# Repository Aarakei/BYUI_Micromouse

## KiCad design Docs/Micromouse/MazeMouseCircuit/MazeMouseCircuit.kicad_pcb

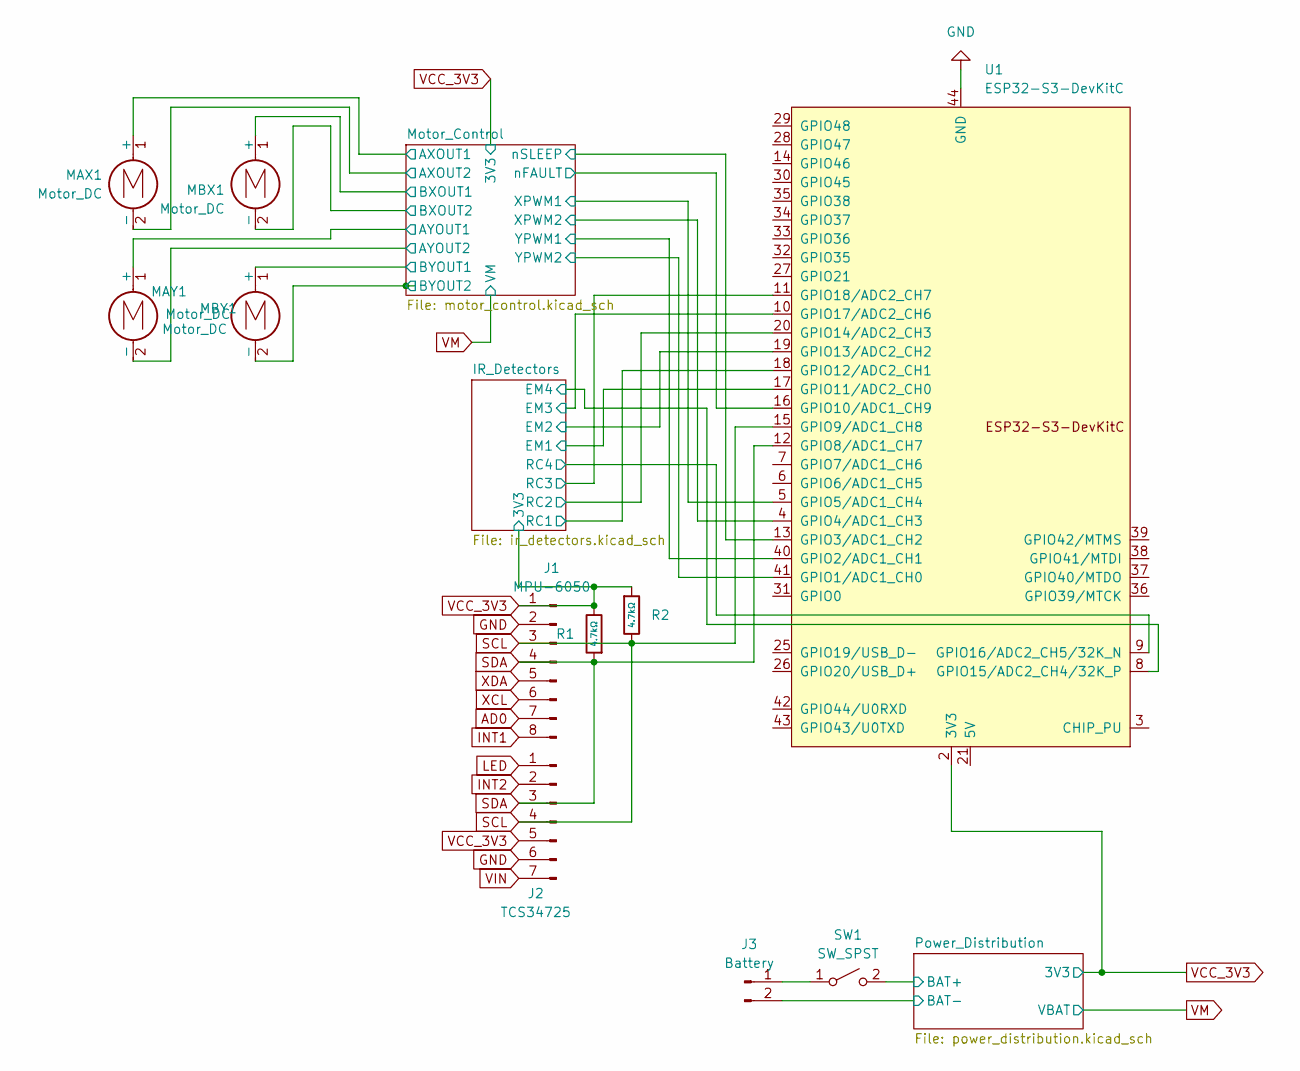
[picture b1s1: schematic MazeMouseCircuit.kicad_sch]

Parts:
J1: MPU-6050; PinHeader_1x08_P2.54mm_Vertical
J2: TCS34725; PinHeader_1x07_P2.54mm_Vertical
J3: Battery; PhoenixContact_GMSTBVA_2,5_2-G_1x02_P7.50mm_Vertical
MAX1: Motor_DC; PinHeader_2x01_P2.54mm_Vertical
MAY1: Motor_DC; PinHeader_2x01_P2.54mm_Vertical
MBX1: Motor_DC; PinHeader_2x01_P2.54mm_Vertical
MBY1: Motor_DC; PinHeader_2x01_P2.54mm_Vertical
R1, R2: 4.7kΩ; R_0402; Overload Voltage (Max) 50V; Tolerance ±1%; Part 0402WGF4701TCE; LCSC C25900
SW1: SW_SPST; SW_DIP_SPSTx01_Slide_9.78x4.72mm_W8.61mm_P2.54mm
U1: ESP32-S3-DevKitC; ESP32-S3-DevKitC-Dual-USB-C

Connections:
/IR_Detectors/EM1: U1.17 (GPIO11/ADC2_CH0); also elsewhere on the board
/IR_Detectors/EM2: U1.19 (GPIO13/ADC2_CH2); also elsewhere on the board
/IR_Detectors/EM3: U1.10 (GPIO17/ADC2_CH6); also elsewhere on the board
/IR_Detectors/EM4: U1.8 (GPIO15/ADC2_CH4/32K_P); also elsewhere on the board
/IR_Detectors/RC1: U1.18 (GPIO12/ADC2_CH1); also elsewhere on the board
/IR_Detectors/RC2: U1.20 (GPIO14/ADC2_CH3); also elsewhere on the board
/IR_Detectors/RC3: U1.11 (GPIO18/ADC2_CH7); also elsewhere on the board
/IR_Detectors/RC4: U1.9 (GPIO16/ADC2_CH5/32K_N); also elsewhere on the board
/Motor_Control/AXOUT1: MAX1.1 (+); also elsewhere on the board
/Motor_Control/AXOUT2: MAX1.2 (-); also elsewhere on the board
/Motor_Control/AYOUT1: MAY1.1 (+); also elsewhere on the board
/Motor_Control/AYOUT2: MAY1.2 (-); also elsewhere on the board
/Motor_Control/BXOUT1: MBX1.1 (+); also elsewhere on the board
/Motor_Control/BXOUT2: MBX1.2 (-); also elsewhere on the board
/Motor_Control/BYOUT1: MBY1.1 (+); also elsewhere on the board
/Motor_Control/BYOUT2: MBY1.2 (-); also elsewhere on the board
/Motor_Control/XPWM1: U1.5 (GPIO5/ADC1_CH4); also elsewhere on the board
/Motor_Control/XPWM2: U1.4 (GPIO4/ADC1_CH3); also elsewhere on the board
/Motor_Control/YPWM1: U1.40 (GPIO2/ADC1_CH1); also elsewhere on the board
/Motor_Control/YPWM2: U1.41 (GPIO1/ADC1_CH0); also elsewhere on the board
/Motor_Control/nFAULT: U1.16 (GPIO10/ADC1_CH9); also elsewhere on the board
/Motor_Control/nSLEEP: U1.13 (GPIO3/ADC1_CH2); also elsewhere on the board
/Power_Distribution/BAT+: SW1.2 (B); also elsewhere on the board
AD0: J1.7
GND: J1.2, J2.6, J3.2, U1.22 (GND), U1.23 (GND), U1.24 (GND), U1.44 (GND); also elsewhere on the board
INT1: J1.8
INT2: J2.2
LED: J2.1
unnamed: J3.1, SW1.1 (A)
SCL: J1.3, J2.4, R2.2, U1.15 (GPIO9/ADC1_CH8)
SDA: J1.4, J2.3, R1.1, U1.12 (GPIO8/ADC1_CH7)
VCC_3V3: J1.1, J2.5, R1.2, R2.1, U1.1 (3V3), U1.2 (3V3); also elsewhere on the board
VIN: J2.7
XCL: J1.6
XDA: J1.5

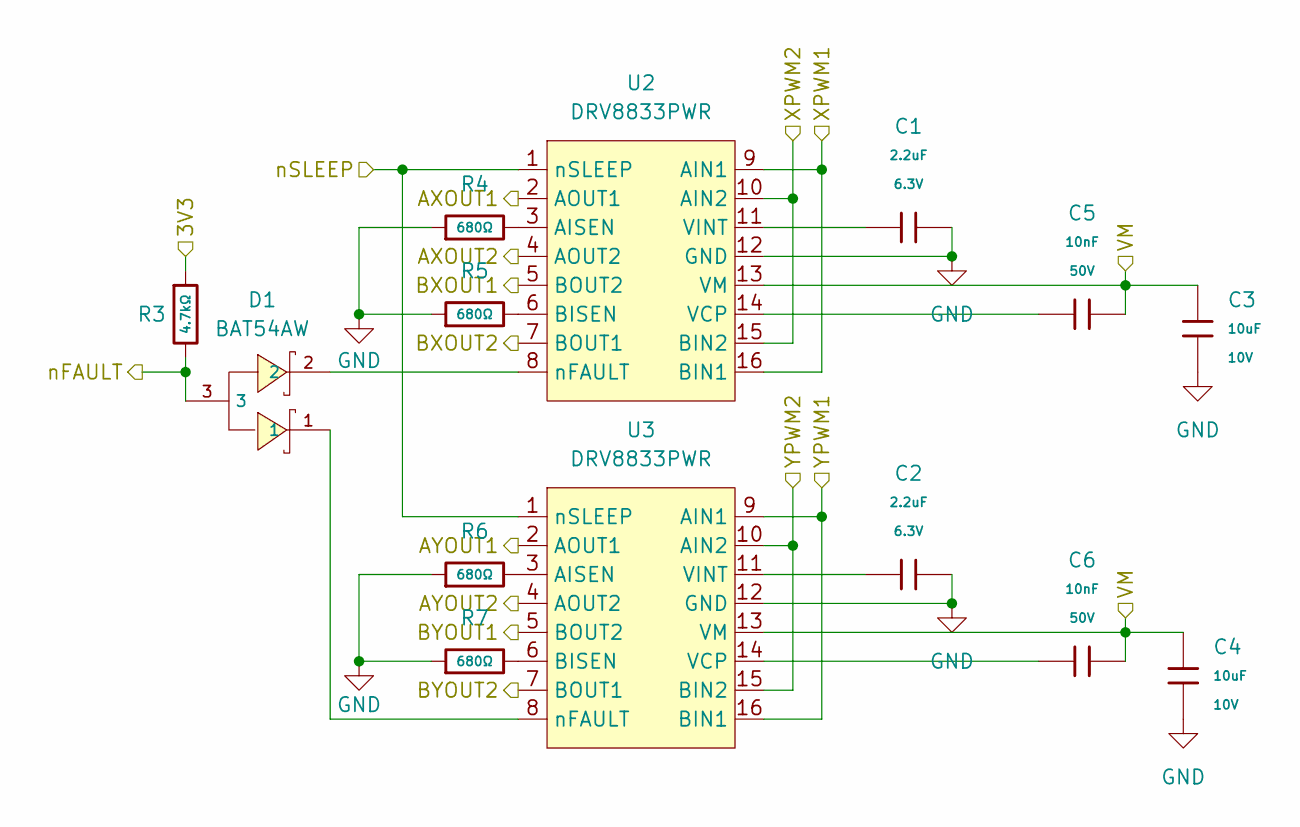
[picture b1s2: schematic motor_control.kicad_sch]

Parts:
C1, C2: 2.2uF; C_0402; Voltage Rated 6.3V; Tolerance ±20%; Part CL05A225MQ5NSNC; LCSC C12530
C3, C4: 10uF; C_0603; Voltage Rated 10V; Tolerance ±10%; Part CL10A106KP8NNNC; LCSC C19702
C5, C6: 10nF; C_0402; Voltage Rated 50V; Tolerance ±10%; Part CL05B103KB5NNNC; LCSC C15195
D1: BAT54AW; SOT-323-3_L2.0-W1.3-P1.30-LS2.3-BR; Part BAT54AW; LCSC C22466374
R3: 4.7kΩ; R_0402; Overload Voltage (Max) 50V; Tolerance ±1%; Part 0402WGF4701TCE; LCSC C25900
R4, R5, R6, R7: 680Ω; R_0402; Overload Voltage (Max) 50V; Tolerance ±1%; Part 0402WGF6800TCE; LCSC C25130
U2, U3: DRV8833PWR; TSSOP-16_4.4x5mm_P0.65mm

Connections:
/Motor_Control/AXOUT1: U2.2 (AOUT1); also elsewhere on the board
/Motor_Control/AXOUT2: U2.4 (AOUT2); also elsewhere on the board
/Motor_Control/AYOUT1: U3.2 (AOUT1); also elsewhere on the board
/Motor_Control/AYOUT2: U3.4 (AOUT2); also elsewhere on the board
/Motor_Control/BXOUT1: U2.5 (BOUT2); also elsewhere on the board
/Motor_Control/BXOUT2: U2.7 (BOUT1); also elsewhere on the board
/Motor_Control/BYOUT1: U3.5 (BOUT2); also elsewhere on the board
/Motor_Control/BYOUT2: U3.7 (BOUT1); also elsewhere on the board
/Motor_Control/XPWM1: U2.9 (AIN1), U2.16 (BIN1); also elsewhere on the board
/Motor_Control/XPWM2: U2.10 (AIN2), U2.15 (BIN2); also elsewhere on the board
/Motor_Control/YPWM1: U3.9 (AIN1), U3.16 (BIN1); also elsewhere on the board
/Motor_Control/YPWM2: U3.10 (AIN2), U3.15 (BIN2); also elsewhere on the board
/Motor_Control/nFAULT: D1.3, R3.2; also elsewhere on the board
/Motor_Control/nSLEEP: U2.1 (nSLEEP), U3.1 (nSLEEP); also elsewhere on the board
GND: C1.2, C2.2, C3.1, C4.1, R4.1, R5.1, R6.1, R7.1, U2.12 (GND), U3.12 (GND); also elsewhere on the board
unnamed: R4.2, U2.3 (AISEN)
unnamed: R5.2, U2.6 (BISEN)
unnamed: C5.2, U2.14 (VCP)
unnamed: C1.1, U2.11 (VINT)
unnamed: D1.2, U2.8 (nFAULT)
unnamed: R6.2, U3.3 (AISEN)
unnamed: R7.2, U3.6 (BISEN)
unnamed: C6.2, U3.14 (VCP)
unnamed: C2.1, U3.11 (VINT)
unnamed: D1.1, U3.8 (nFAULT)
VCC_3V3: R3.1; also elsewhere on the board
VM: C3.2, C4.2, C5.1, C6.1, U2.13 (VM), U3.13 (VM); also elsewhere on the board

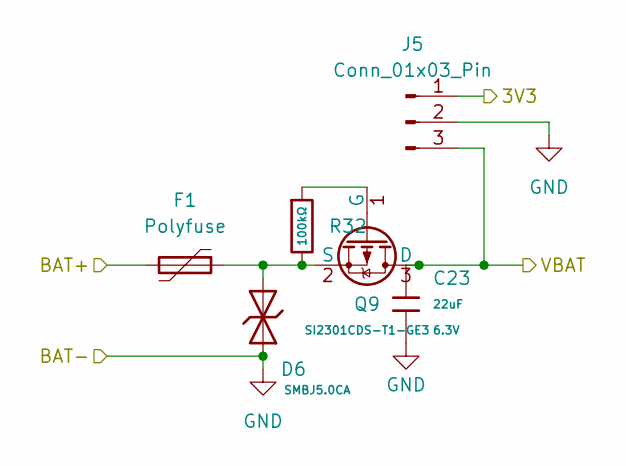
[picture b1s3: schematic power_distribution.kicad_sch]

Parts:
C23: 22uF; C_0603; Voltage Rated 6.3V; Tolerance ±20%; Part CL10A226MQ8NRNC; LCSC C59461
D6: SMBJ5.0CA; D_SMB; Part SMBJ5.0CA; LCSC C19077559
F1: Polyfuse; Fuse_0402_1005Metric
J5: Conn_01x03_Pin; PinHeader_1x03_P2.54mm_Vertical
Q9: SI2301CDS-T1-GE3; Q_SOT-23; Part SI2301CDS-T1-GE3; LCSC C10487
R32: 100kΩ; R_0603; Overload Voltage (Max) 75V; Tolerance ±1%; Part 0603WAF1003T5E; LCSC C25803

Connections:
/Power_Distribution/BAT+: F1.2; also elsewhere on the board
GND: C23.2, D6.2, J5.2; also elsewhere on the board
unnamed: Q9.1 (G), R32.1
unnamed: D6.1, F1.1, Q9.2 (S), R32.2
VCC_3V3: J5.1; also elsewhere on the board
VM: C23.1, J5.3, Q9.3 (D); also elsewhere on the board

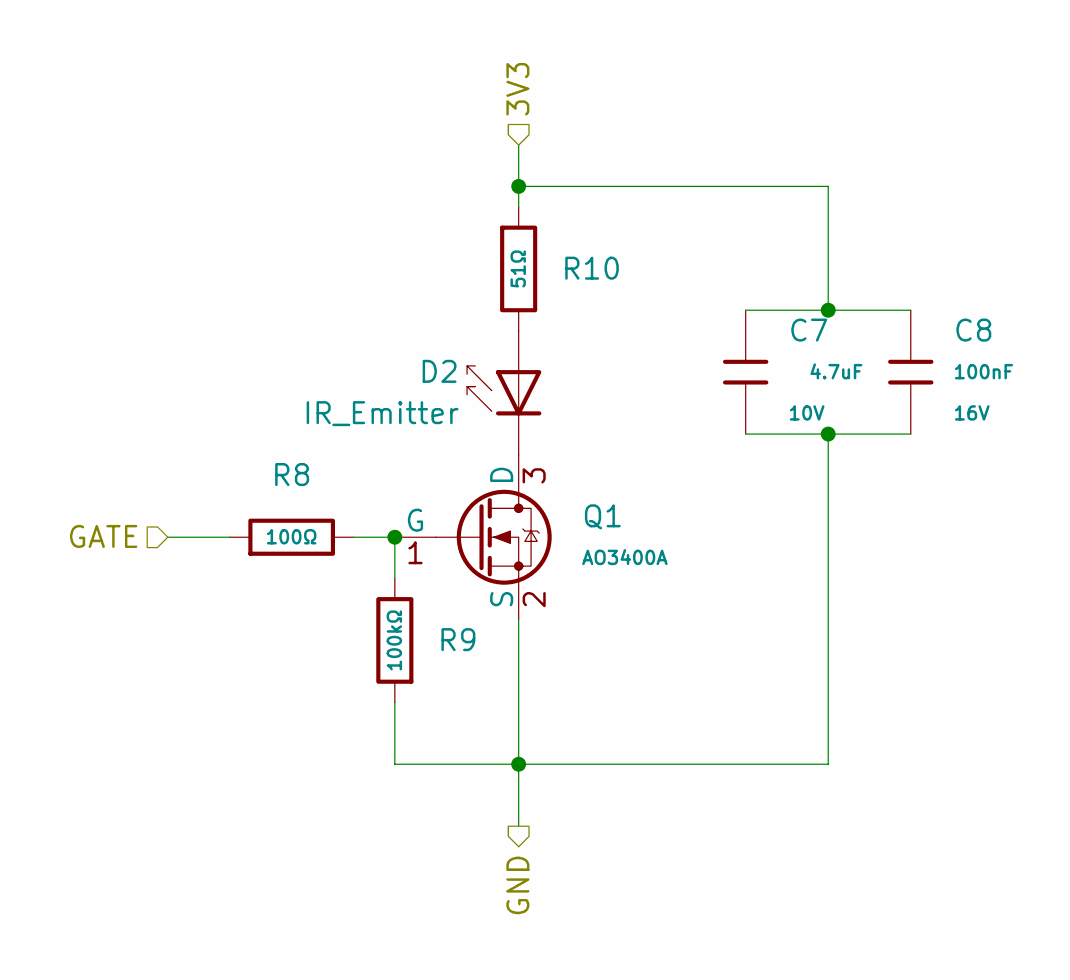
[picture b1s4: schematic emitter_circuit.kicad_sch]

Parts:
C7: 4.7uF; C_0402; Voltage Rated 10V; Tolerance ±20%; Part CL05A475MP5NRNC; LCSC C23733
C8: 100nF; C_0402; Voltage Rated 16V; Tolerance ±10%; Part CL05B104KO5NNNC; LCSC C1525
D2: IR_Emitter; LED_D5.0mm_Horizontal_O1.27mm_Z3.0mm_IRBlack
Q1: AO3400A; Q_SOT-23; Part AO3400A; LCSC C20917
R8: 100Ω; R_0402; Overload Voltage (Max) 50V; Tolerance ±1%; Part 0402WGF1000TCE; LCSC C25076
R9: 100kΩ; R_0603; Overload Voltage (Max) 75V; Tolerance ±1%; Part 0603WAF1003T5E; LCSC C25803
R10: 51Ω; R_0402; Overload Voltage (Max) 50V; Tolerance ±1%; Part 0402WGF510JTCE; LCSC C25125

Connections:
/IR_Detectors/EM1: R8.1; also elsewhere on the board
GND: C7.2, C8.2, Q1.2 (S), R9.1; also elsewhere on the board
unnamed: D2.2 (A), R10.2
unnamed: D2.1 (K), Q1.3 (D)
unnamed: Q1.1 (G), R8.2, R9.2
VCC_3V3: C7.1, C8.1, R10.1; also elsewhere on the board

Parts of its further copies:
C11, C15, C19: 4.7uF; C_0402; Voltage Rated 10V; Tolerance ±20%; Part CL05A475MP5NRNC; LCSC C23733
C12, C16, C20: 100nF; C_0402; Voltage Rated 16V; Tolerance ±10%; Part CL05B104KO5NNNC; LCSC C1525
D3, D4, D5: IR_Emitter; LED_D5.0mm_Horizontal_O1.27mm_Z3.0mm_IRBlack
Q3, Q5, Q7: AO3400A; Q_SOT-23; Part AO3400A; LCSC C20917
R14, R20, R26: 100Ω; R_0402; Overload Voltage (Max) 50V; Tolerance ±1%; Part 0402WGF1000TCE; LCSC C25076
R15, R21, R27: 100kΩ; R_0603; Overload Voltage (Max) 75V; Tolerance ±1%; Part 0603WAF1003T5E; LCSC C25803
R16, R22, R28: 51Ω; R_0402; Overload Voltage (Max) 50V; Tolerance ±1%; Part 0402WGF510JTCE; LCSC C25125

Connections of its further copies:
/IR_Detectors/EM2: R14.1; also elsewhere on the board
/IR_Detectors/EM3: R20.1; also elsewhere on the board
/IR_Detectors/EM4: R26.1; also elsewhere on the board
GND: C11.2, C12.2, C15.2, C16.2, C19.2, C20.2, Q3.2 (S), Q5.2 (S), Q7.2 (S), R15.1, R21.1, R27.1; also elsewhere on the board
unnamed: D3.2 (A), R16.2
unnamed: D3.1 (K), Q3.3 (D)
unnamed: D4.2 (A), R22.2
unnamed: D4.1 (K), Q5.3 (D)
unnamed: D5.2 (A), R28.2
unnamed: D5.1 (K), Q7.3 (D)
unnamed: Q3.1 (G), R14.2, R15.2
unnamed: Q5.1 (G), R20.2, R21.2
unnamed: Q7.1 (G), R26.2, R27.2
VCC_3V3: C11.1, C12.1, C15.1, C16.1, C19.1, C20.1, R16.1, R22.1, R28.1; also elsewhere on the board

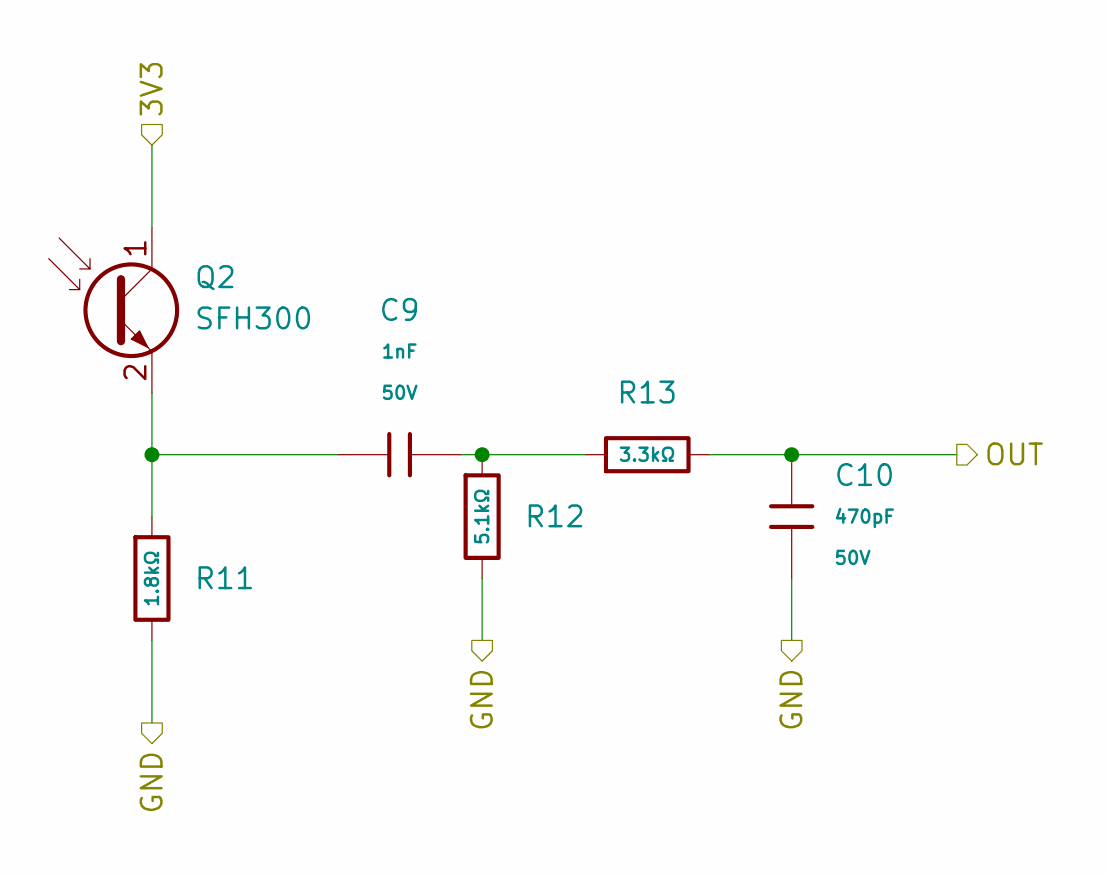
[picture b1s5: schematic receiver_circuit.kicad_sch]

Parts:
C9: 1nF; C_0402; Voltage Rated 50V; Tolerance ±10%; Part 0402B102K500NT; LCSC C1523
C10: 470pF; C_0402; Voltage Rated 50V; Tolerance ±10%; Part 0402B471K500NT; LCSC C1537
Q2: SFH300; LED_D5.0mm_Horizontal_O1.27mm_Z3.0mm_Clear
R11: 1.8kΩ; R_0805; Overload Voltage (Max) 150V; Tolerance ±1%; Part 0805W8F1801T5E; LCSC C17398
R12: 5.1kΩ; R_0402; Overload Voltage (Max) 50V; Tolerance ±1%; Part 0402WGF5101TCE; LCSC C25905
R13: 3.3kΩ; R_0402; Overload Voltage (Max) 50V; Tolerance ±1%; Part 0402WGF3301TCE; LCSC C25890

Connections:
/IR_Detectors/RC1: C10.1, R13.2; also elsewhere on the board
GND: C10.2, R11.2, R12.2; also elsewhere on the board
unnamed: C9.2, R12.1, R13.1
unnamed: C9.1, Q2.2 (E), R11.1
VCC_3V3: Q2.1 (C); also elsewhere on the board

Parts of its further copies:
C13, C17, C21: 1nF; C_0402; Voltage Rated 50V; Tolerance ±10%; Part 0402B102K500NT; LCSC C1523
C14, C18, C22: 470pF; C_0402; Voltage Rated 50V; Tolerance ±10%; Part 0402B471K500NT; LCSC C1537
Q4, Q6, Q8: SFH300; LED_D5.0mm_Horizontal_O1.27mm_Z3.0mm_Clear
R17, R23, R29: 1.8kΩ; R_0805; Overload Voltage (Max) 150V; Tolerance ±1%; Part 0805W8F1801T5E; LCSC C17398
R18, R24, R30: 5.1kΩ; R_0402; Overload Voltage (Max) 50V; Tolerance ±1%; Part 0402WGF5101TCE; LCSC C25905
R19, R25, R31: 3.3kΩ; R_0402; Overload Voltage (Max) 50V; Tolerance ±1%; Part 0402WGF3301TCE; LCSC C25890

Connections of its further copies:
/IR_Detectors/RC2: C14.1, R19.2; also elsewhere on the board
/IR_Detectors/RC3: C18.1, R25.2; also elsewhere on the board
/IR_Detectors/RC4: C22.1, R31.2; also elsewhere on the board
GND: C14.2, C18.2, C22.2, R17.2, R18.2, R23.2, R24.2, R29.2, R30.2; also elsewhere on the board
unnamed: C13.2, R18.1, R19.1
unnamed: C17.2, R24.1, R25.1
unnamed: C21.2, R30.1, R31.1
unnamed: C13.1, Q4.2 (E), R17.1
unnamed: C17.1, Q6.2 (E), R23.1
unnamed: C21.1, Q8.2 (E), R29.1
VCC_3V3: Q4.1 (C), Q6.1 (C), Q8.1 (C); also elsewhere on the board

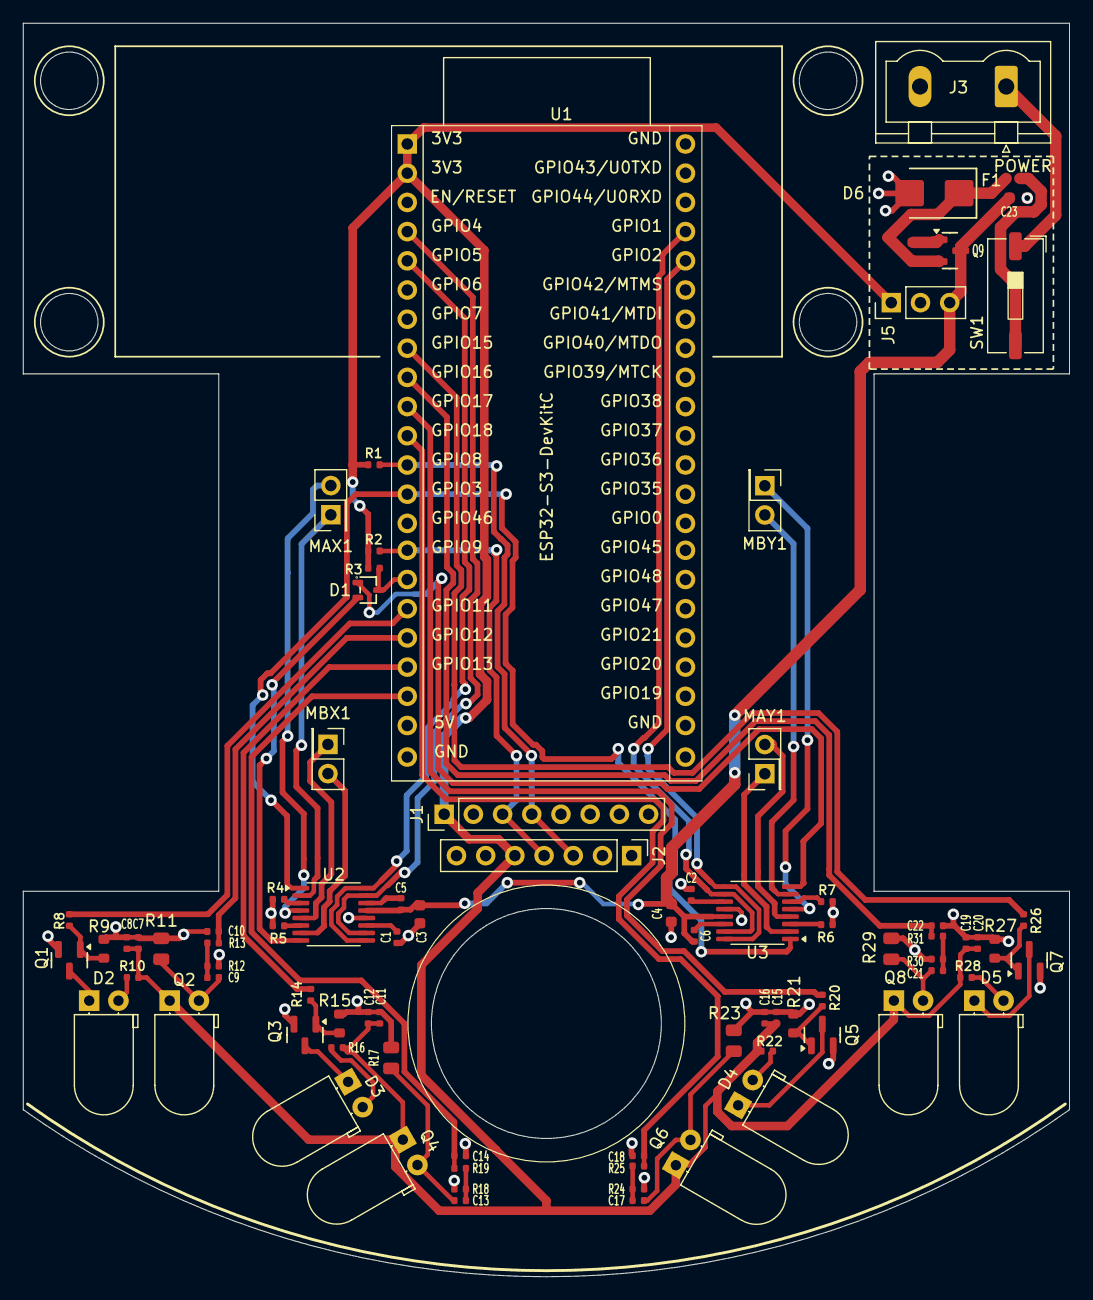
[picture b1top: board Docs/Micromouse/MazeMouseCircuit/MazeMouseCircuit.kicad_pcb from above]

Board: 2 copper layers, 91.0 x 109.0 mm, 83 parts (0 on the bottom side), 61 nets.

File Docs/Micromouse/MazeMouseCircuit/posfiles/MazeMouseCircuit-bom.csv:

Reference	Qty	Value	DNP	Exclude from BOM	Exclude from Board	Footprint	Datasheet
C1,C2	2	2.2uF				PCM_JLCPCB:C_0402	https://www.lcsc.com/datasheet/lcsc_datasheet_2304140030_Sam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
C3,C4	2	10uF				PCM_JLCPCB:C_0603	https://www.lcsc.com/datasheet/lcsc_datasheet_2304140030_Sam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
C5,C6	2	10nF				PCM_JLCPCB:C_0402	https://www.lcsc.com/datasheet/lcsc_datasheet_2304140030_Sam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
C7,C11,C15,C19	4	4.7uF				PCM_JLCPCB:C_0402	https://www.lcsc.com/datasheet/lcsc_datasheet_2304140030_Sam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
C8,C12,C16,C20	4	100nF				PCM_JLCPCB:C_0402	https://www.lcsc.com/datasheet/lcsc_datasheet_2304140030_Sam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
C9,C13,C17,C21	4	1nF				PCM_JLCPCB:C_0402	https://www.lcsc.com/datasheet/lcsc_datasheet_2304140030_FH-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
C10,C14,C18,C22	4	470pF				PCM_JLCPCB:C_0402	https://www.lcsc.com/datasheet/lcsc_datasheet_2304140030_FH-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
C23	1	22uF				PCM_JLCPCB:C_0603	https://www.lcsc.com/datasheet/lcsc_datasheet_2304140030_Sam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
D1	1	BAT54AW				PCM_JLCPCB:SOT-323-3_L2.0-W1.3-P1.30-LS2.3-BR	https://wmsc.lcsc.com/wmsc/upload/file/pdf/v2/lcsc/240619160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
D2,D3,D4,D5	4	IR_Emitter				LED_THT:LED_D5.0mm_Horizontal_O1.27mm_Z3.0mm_IRBlack	http://www.everlight.com/file/ProductFile/IR204-A.pdf
D6	1	SMBJ5.0CA				PCM_JLCPCB:D_SMB	https://wmsc.lcsc.com/wmsc/upload/file/pdf/v2/lcsc/231228093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
F1	1	Polyfuse				Fuse:Fuse_0402_1005Metric	~
J1	1	MPU-6050				Connector_PinHeader_2.54mm:PinHeader_1x08_P2.54mm_Vertical	~
J2	1	TCS34725				Connector_PinHeader_2.54mm:PinHeader_1x07_P2.54mm_Vertical	~
J3	1	Battery				Connector_Phoenix_GMSTB:PhoenixContact_GMSTBVA_2,5_2-G_1x02_P7.50mm_Vertical	~
J5	1	Conn_01x03_Pin				Connector_PinHeader_2.54mm:PinHeader_1x03_P2.54mm_Vertical	~
MAX1,MAY1,MBX1,MBY1	4	Motor_DC				Connector_PinHeader_2.54mm:PinHeader_2x01_P2.54mm_Vertical	~
Q1,Q3,Q5,Q7	4	AO3400A				PCM_JLCPCB:Q_SOT-23	https://www.lcsc.com/datasheet/lcsc_datasheet_1811081213_Alp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
Q2,Q4,Q6,Q8	4	SFH300				LED_THT:LED_D5.0mm_Horizontal_O1.27mm_Z3.0mm_Clear	http://www.osram-os.com/Graphics/XPic2/00101785_0.pdf
Q9	1	SI2301CDS-T1-GE3				PCM_JLCPCB:Q_SOT-23	https://www.lcsc.com/datasheet/lcsc_datasheet_1808272021_Vis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
R1,R2,R3	3	4.7kΩ				PCM_JLCPCB:R_0402	https://www.lcsc.com/datasheet/lcsc_datasheet_2206010045_UNI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
R4,R5,R6,R7	4	680Ω				PCM_JLCPCB:R_0402	https://www.lcsc.com/datasheet/lcsc_datasheet_2205311900_UNI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
R8,R14,R20,R26	4	100Ω				PCM_JLCPCB:R_0402	https://www.lcsc.com/datasheet/lcsc_datasheet_2205311900_UNI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
R9,R15,R21,R27,R32	5	100kΩ				PCM_JLCPCB:R_0603	https://www.lcsc.com/datasheet/lcsc_datasheet_2206010045_UNI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
R10,R16,R22,R28	4	51Ω				PCM_JLCPCB:R_0402	https://www.lcsc.com/datasheet/lcsc_datasheet_2205311900_UNI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
R11,R17,R23,R29	4	1.8kΩ				PCM_JLCPCB:R_0805	https://www.lcsc.com/datasheet/lcsc_datasheet_2206010216_UNI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
R12,R18,R24,R30	4	5.1kΩ				PCM_JLCPCB:R_0402	https://www.lcsc.com/datasheet/lcsc_datasheet_2206010045_UNI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
R13,R19,R25,R31	4	3.3kΩ				PCM_JLCPCB:R_0402	https://www.lcsc.com/datasheet/lcsc_datasheet_2206010045_UNI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
SW1	1	SW_SPST				Button_Switch_SMD:SW_DIP_SPSTx01_Slide_9.78x4.72mm_W8.61mm_P2.54mm	~
U1	1	ESP32-S3-DevKitC				PCM_Espressif:ESP32-S3-DevKitC-Dual-USB-C	
U2,U3	2	DRV8833PWR				Package_SO:TSSOP-16_4.4x5mm_P0.65mm	https://www.lcsc.com/datasheet/C544801.pdf

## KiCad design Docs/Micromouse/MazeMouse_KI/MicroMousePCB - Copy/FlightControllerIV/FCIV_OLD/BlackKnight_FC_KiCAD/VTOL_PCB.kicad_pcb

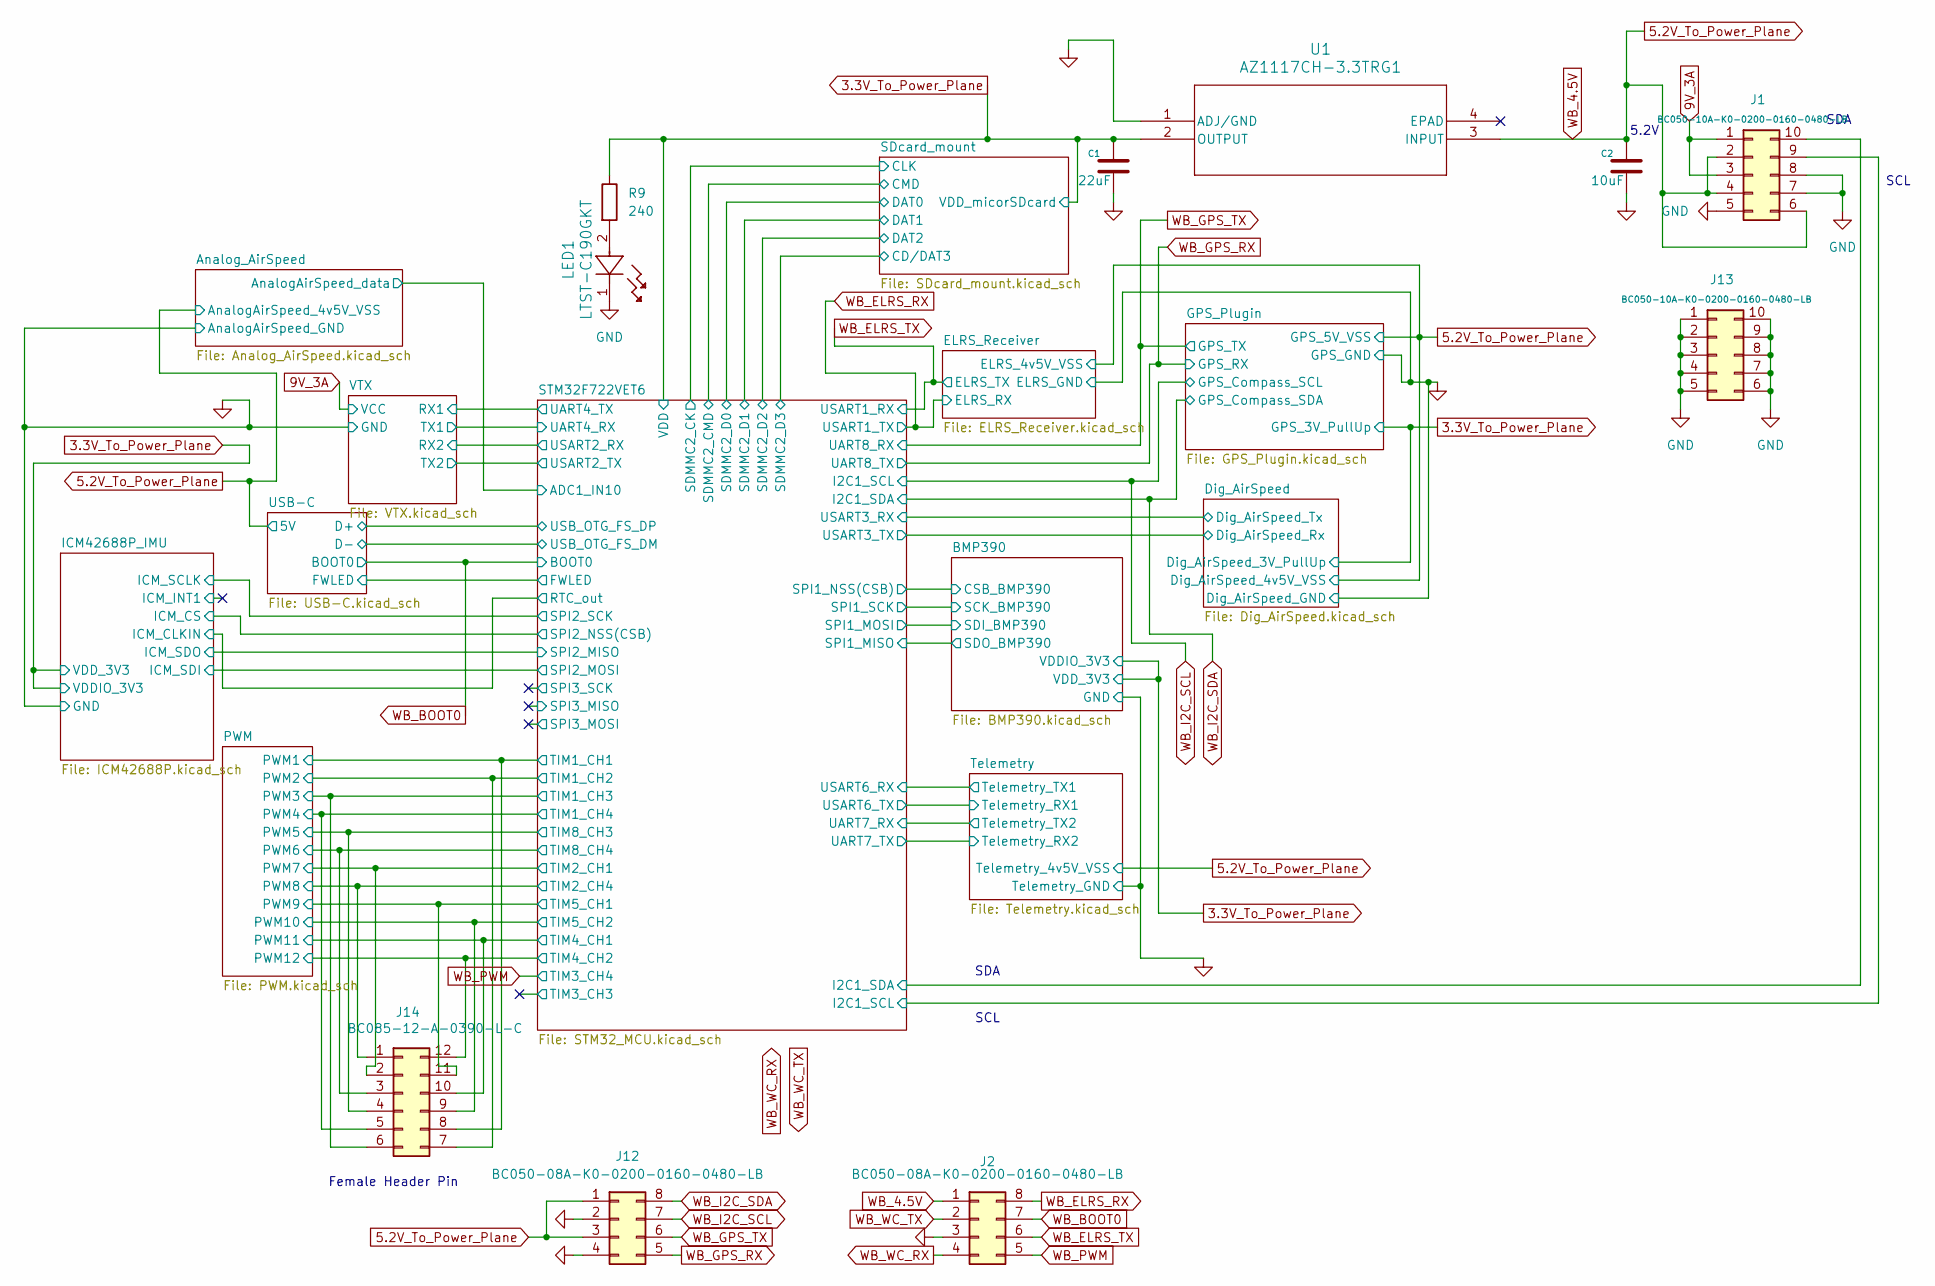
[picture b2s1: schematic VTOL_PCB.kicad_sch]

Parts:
C1: 22uF; C_0603_1608Metric; Manufacturer_Part_Number CL10A226MP8NUNE; JLCPCB Part # C86295
C2: 10uF; C_0603_1608Metric; Manufacturer_Part_Number KAM15CT70E106KT; JLCPCB Part # C19702
J1, J13: BC050-10A-K0-0200-0160-0480-LB; PinHeader_2x05_P1.00mm_Vertical_SMD; Manufacturer_Part_Number BC050-10A-K0-0200-0160-0480-LB; JLCPCB Part # C5952679
J2, J12: BC050-08A-K0-0200-0160-0480-LB; PinHeader_2x04_P1.00mm_Vertical_SMD; Manufacturer_Part_Number BC050-08A-K0-0200-0160-0480-LB; JLCPCB Part # C5557054
J14: BC085-12-A-0390-L-C; PinSocket_2x06_P1.00mm_Vertical_SMD; Manufacturer_Part_Number BC085-12-A-0390-L-C; JLCPCB Part # C5952752
LED1: LTST-C190GKT; LTST-C190CKT; Manufacturer_Part_Number LTST-C190GKT; JLCPCB Part # C125093
R9: 240; R_0603_1608Metric; Manufacturer_Part_Number RC0603FR-07240RL; JLCPCB Part # C114613
U1: AZ1117CH-3.3TRG1; SOT-223_DIO; Manufacturer_Part_Number AZ1117CH-3.3TRG1; JLCPCB Part # C92102

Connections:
3.3V_To_Power_Plane: C1.1, R9.1, U1.2 (OUTPUT); also elsewhere on the board
5.2V_To_Power_Plane: C2.1, J1.2, J1.4, J1.6, J2.1, J12.1, J12.3, U1.3 (INPUT); also elsewhere on the board
9V_3A: J1.1, J1.3; also elsewhere on the board
/PWM/PWM1: J14.8; also elsewhere on the board
/PWM/PWM2: J14.7; also elsewhere on the board
/PWM/PWM3: J14.6; also elsewhere on the board
/PWM/PWM4: J14.5; also elsewhere on the board
/PWM/PWM5: J14.4; also elsewhere on the board
/PWM/PWM6: J14.3; also elsewhere on the board
/PWM/PWM7: J14.2; also elsewhere on the board
/PWM/PWM8: J14.1; also elsewhere on the board
/PWM/PWM9: J14.11; also elsewhere on the board
/PWM/PWM10: J14.9; also elsewhere on the board
/PWM/PWM11: J14.10; also elsewhere on the board
/PWM/PWM12: J14.12; also elsewhere on the board
GND: C1.2, C2.2, J1.5, J1.7, J1.8, J2.3, J12.2, J12.4, J13.1, J13.2, J13.3, J13.4, J13.5, J13.6, J13.7, J13.8, J13.9, J13.10, LED1.1, U1.1 (ADJ/GND); also elsewhere on the board
unnamed: LED1.2, R9.2
WB_BOOT0: J2.7; also elsewhere on the board
WB_ELRS_RX: J2.8; also elsewhere on the board
WB_ELRS_TX: J2.6; also elsewhere on the board
WB_GPS_RX: J12.5; also elsewhere on the board
WB_GPS_TX: J12.6; also elsewhere on the board
WB_I2C_SCL: J1.9, J12.7; also elsewhere on the board
WB_I2C_SDA: J1.10, J12.8; also elsewhere on the board
WB_PWM: J2.5; also elsewhere on the board
WB_WC_RX: J2.4
WB_WC_TX: J2.2

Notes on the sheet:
5.2V
Female Header Pin
SDA
SCL

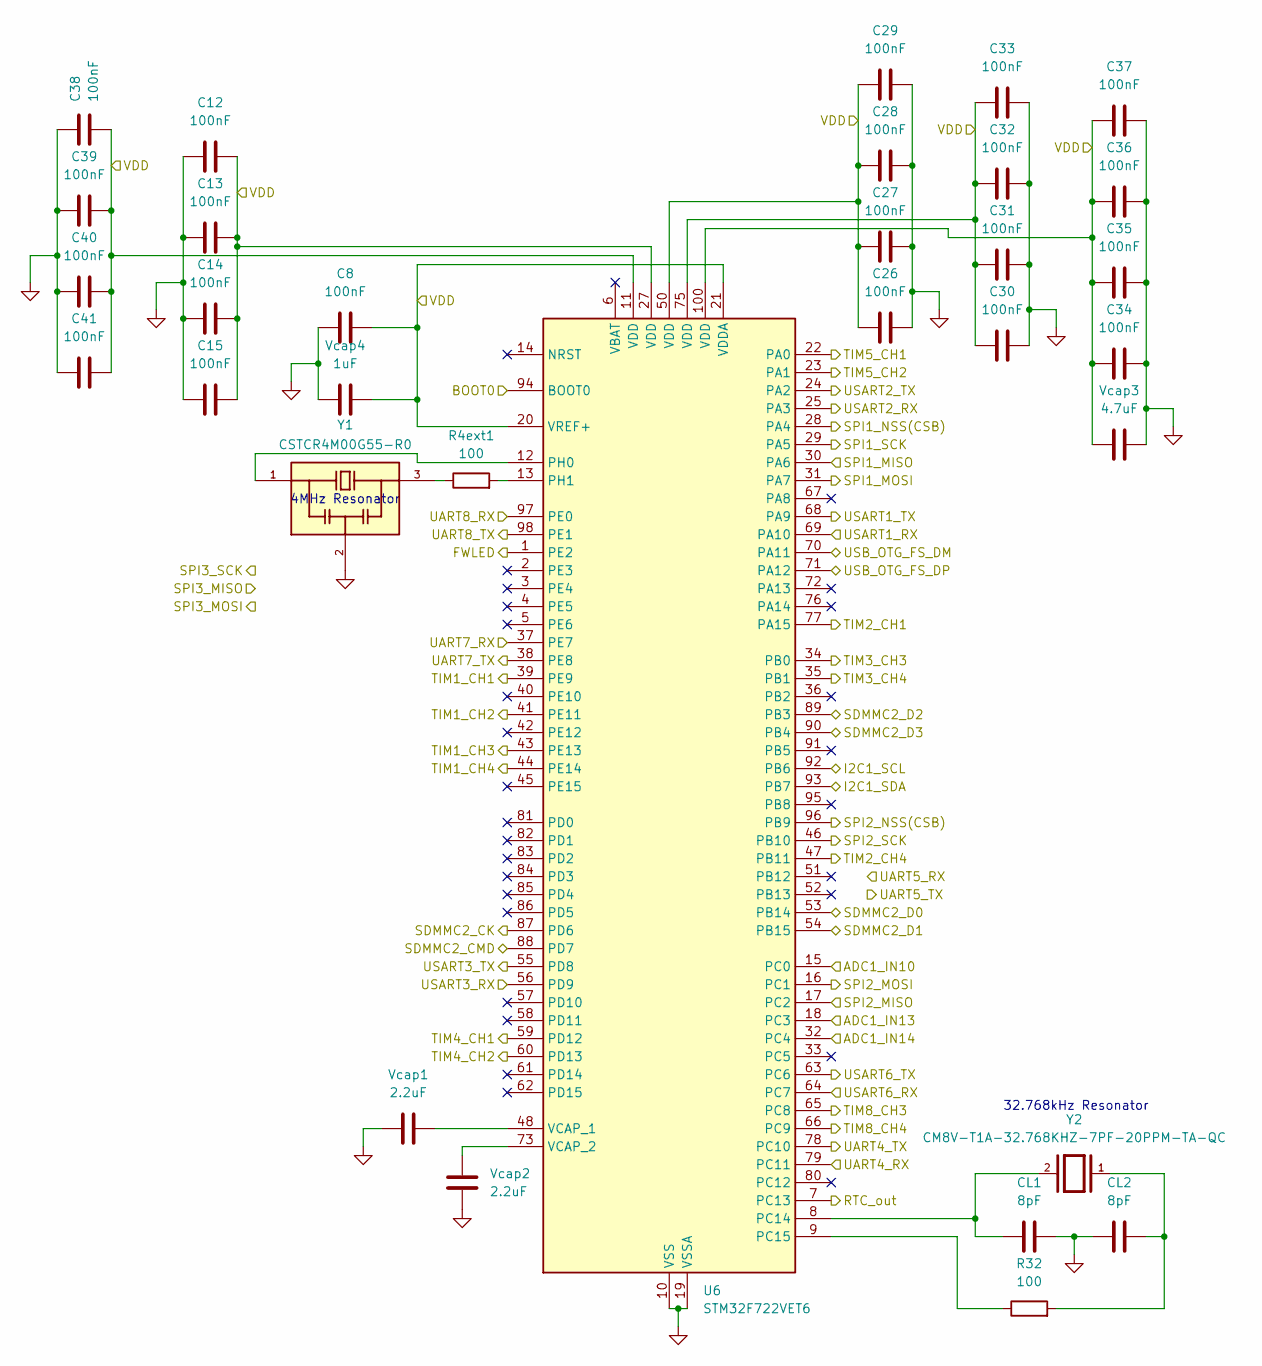
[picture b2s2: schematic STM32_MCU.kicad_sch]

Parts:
C8, C12, C13, C14, C15, C26, C27, C28, C29, C30, C31, C32, C33, C34, C35, C36, C37, C38, C39, C40, C41: 100nF; C_0603_1608Metric; Manufacturer_Part_Number CL10B104KA8NNNC; JLCPCB Part # C1591
CL1, CL2: 8pF; C_0603_1608Metric; Manufacturer_Part_Number CL05C080DB51PNC; JLCPCB Part # C346204
R4ext1, R32: 100; R_0603_1608Metric; Manufacturer_Part_Number CRCW0603100RFKEA; JLCPCB Part # C105588
U6: STM32F722VET6; LQFP-100_14x14mm_P0.5mm; JLCPCB Part # C132372
Vcap1, Vcap2: 2.2uF; C_0603_1608Metric; Manufacturer_Part_Number CL10A225KO8NNNC; JLCPCB Part # C23630
Vcap3: 4.7uF; C_0603_1608Metric; Manufacturer_Part_Number CL10A475KP8NNNC; JLCPCB Part # C19666
Vcap4: 1uF; C_0603_1608Metric; Manufacturer_Part_Number C0603C104K5RACTU; JLCPCB Part # C15849
Y1: CSTCR4M00G55-R0; OSC_CSTCR4M00G55-R0; PARTREV JGC42-8797; JLCPCB Part # C91588
Y2: CM8V-T1A-32.768KHZ-7PF-20PPM-TA-QC; Crystal_SMD_MicroCrystal_CC8V-T1A-2Pin_2.0x1.2mm; PARTREV 8.1/11.2018; JLCPCB Part # C5136974

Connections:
3.3V_To_Power_Plane: C8.2, C12.2, C13.2, C14.2, C15.2, C26.1, C27.1, C28.1, C29.1, C30.1, C31.1, C32.1, C33.1, C34.1, C35.1, C36.1, C37.1, C38.2, C39.2, C40.2, C41.2, U6.11 (VDD), U6.20 (VREF+), U6.21 (VDDA), U6.27 (VDD), U6.50 (VDD), U6.75 (VDD), U6.100 (VDD), Vcap3.1, Vcap4.2; also elsewhere on the board
/Analog_AirSpeed/AnalogAirSpeed_data: U6.15 (PC0); also elsewhere on the board
/BMP390/CSB_BMP390: U6.28 (PA4); also elsewhere on the board
/BMP390/SCK_BMP390: U6.29 (PA5); also elsewhere on the board
/BMP390/SDI_BMP390: U6.31 (PA7); also elsewhere on the board
/BMP390/SDO_BMP390: U6.30 (PA6); also elsewhere on the board
/Dig_AirSpeed/Dig_AirSpeed_Rx: U6.55 (PD8); also elsewhere on the board
/Dig_AirSpeed/Dig_AirSpeed_Tx: U6.56 (PD9); also elsewhere on the board
/ICM42688P_IMU/ICM_CLKIN: U6.7 (PC13); also elsewhere on the board
/ICM42688P_IMU/ICM_CS: U6.96 (PB9); also elsewhere on the board
/ICM42688P_IMU/ICM_SCLK: U6.46 (PB10); also elsewhere on the board
/ICM42688P_IMU/ICM_SDI: U6.16 (PC1); also elsewhere on the board
/ICM42688P_IMU/ICM_SDO: U6.17 (PC2); also elsewhere on the board
/PWM/PWM1: U6.39 (PE9); also elsewhere on the board
/PWM/PWM2: U6.41 (PE11); also elsewhere on the board
/PWM/PWM3: U6.43 (PE13); also elsewhere on the board
/PWM/PWM4: U6.44 (PE14); also elsewhere on the board
/PWM/PWM5: U6.65 (PC8); also elsewhere on the board
/PWM/PWM6: U6.66 (PC9); also elsewhere on the board
/PWM/PWM7: U6.77 (PA15); also elsewhere on the board
/PWM/PWM8: U6.47 (PB11); also elsewhere on the board
/PWM/PWM9: U6.22 (PA0); also elsewhere on the board
/PWM/PWM10: U6.23 (PA1); also elsewhere on the board
/PWM/PWM11: U6.59 (PD12); also elsewhere on the board
/PWM/PWM12: U6.60 (PD13); also elsewhere on the board
/SDcard_mount/CD/DAT3: U6.90 (PB4); also elsewhere on the board
/SDcard_mount/CLK: U6.87 (PD6); also elsewhere on the board
/SDcard_mount/CMD: U6.88 (PD7); also elsewhere on the board
/SDcard_mount/DAT0: U6.53 (PB14); also elsewhere on the board
/SDcard_mount/DAT1: U6.54 (PB15); also elsewhere on the board
/SDcard_mount/DAT2: U6.89 (PB3); also elsewhere on the board
/STM32F722VET6/ADC1_IN13: U6.18 (PC3)
/STM32F722VET6/ADC1_IN14: U6.32 (PC4)
/STM32F722VET6/FWLED: U6.1 (PE2); also elsewhere on the board
/STM32F722VET6/TIM3_CH3: U6.34 (PB0)
/STM32F722VET6/UART4_RX: U6.79 (PC11); also elsewhere on the board
/STM32F722VET6/UART4_TX: U6.78 (PC10); also elsewhere on the board
/STM32F722VET6/UART7_RX: U6.37 (PE7); also elsewhere on the board
/STM32F722VET6/UART7_TX: U6.38 (PE8); also elsewhere on the board
/STM32F722VET6/USART2_RX: U6.25 (PA3); also elsewhere on the board
/STM32F722VET6/USART2_TX: U6.24 (PA2); also elsewhere on the board
/STM32F722VET6/USART6_RX: U6.64 (PC7); also elsewhere on the board
/STM32F722VET6/USART6_TX: U6.63 (PC6); also elsewhere on the board
/STM32F722VET6/USB_OTG_FS_DM: U6.70 (PA11); also elsewhere on the board
/STM32F722VET6/USB_OTG_FS_DP: U6.71 (PA12); also elsewhere on the board
GND: C8.1, C12.1, C13.1, C14.1, C15.1, C26.2, C27.2, C28.2, C29.2, C30.2, C31.2, C32.2, C33.2, C34.2, C35.2, C36.2, C37.2, C38.1, C39.1, C40.1, C41.1, CL1.2, CL2.1, U6.10 (VSS), U6.19 (VSSA), U6.26 (VSS), U6.49 (VSS), U6.74 (VSS), U6.99 (VSS), Vcap1.1, Vcap2.2, Vcap3.2, Vcap4.1, Y1.2; also elsewhere on the board
unnamed: CL2.2, R32.2, Y2.1
unnamed: R4ext1.1, Y1.3
unnamed: CL1.1, U6.8 (PC14), Y2.2
unnamed: R32.1, U6.9 (PC15)
unnamed: U6.12 (PH0), Y1.1
unnamed: R4ext1.2, U6.13 (PH1)
unnamed: U6.48 (VCAP_1), Vcap1.2
unnamed: U6.73 (VCAP_2), Vcap2.1
WB_BOOT0: U6.94 (BOOT0); also elsewhere on the board
WB_ELRS_RX: U6.68 (PA9); also elsewhere on the board
WB_ELRS_TX: U6.69 (PA10); also elsewhere on the board
WB_GPS_RX: U6.98 (PE1); also elsewhere on the board
WB_GPS_TX: U6.97 (PE0); also elsewhere on the board
WB_I2C_SCL: U6.92 (PB6); also elsewhere on the board
WB_I2C_SDA: U6.93 (PB7); also elsewhere on the board
WB_PWM: U6.35 (PB1); also elsewhere on the board

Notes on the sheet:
32.768kHz Resonator
4MHz Resonator
